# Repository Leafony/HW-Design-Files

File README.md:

# License

These files are licensed under a [Creative Commons Attribution license(CC-BY)](https://creativecommons.org/licenses/by/4.0/).

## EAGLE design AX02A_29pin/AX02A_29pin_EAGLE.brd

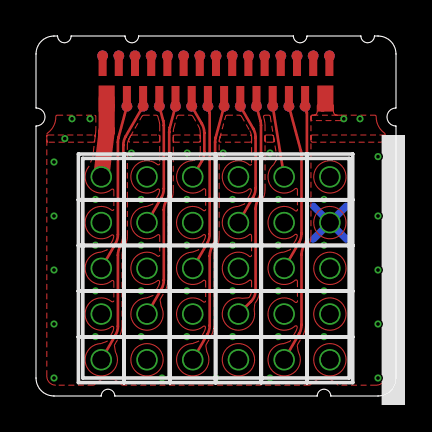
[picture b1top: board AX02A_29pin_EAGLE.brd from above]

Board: 4 copper layers, 20.0 x 20.0 mm, 31 parts (0 on the bottom side), 29 nets.

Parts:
CN561: PW10180TD
DP561, DP562, DP563, DP564, DP565, DP566, DP567, DP568, DP569, DP570, DP571, DP572, DP573, DP574, DP575, DP576, DP577, DP578, DP579, DP580, DP581, DP582, DP583, DP584, DP585, DP586, DP587, DP588, DP589, DP590: DP002T

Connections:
A0: CN561.B6, CN561.F6, DP566.1
A1: CN561.B8, CN561.F8, DP568.1
A2: CN561.B10, CN561.F10, DP570.1
A3: CN561.B12, CN561.F12, DP572.1
A4: CN561.B14, CN561.F14, DP574.1
A5: CN561.B16, CN561.F16, DP576.1
AREF: CN561.B4, CN561.F4, DP564.1
D0: CN561.B18, CN561.F18, DP578.1
D1: CN561.B20, CN561.F20, DP580.1
D2: CN561.B22, CN561.F22, DP582.1
D3: CN561.B24, CN561.F24, DP584.1
D4: CN561.B26, CN561.F26, DP586.1
D5: CN561.B28, CN561.F28, DP588.1
D6: CN561.B7, CN561.F7, DP567.1
D7: CN561.B9, CN561.F9, DP569.1
D8: CN561.B11, CN561.F11, DP571.1
D9: CN561.B13, CN561.F13, DP573.1
D10: CN561.B15, CN561.F15, DP575.1
D11: CN561.B17, CN561.F17, DP577.1
D12: CN561.B19, CN561.F19, DP579.1
D13: CN561.B21, CN561.F21, DP581.1
GND: CN561.B27, CN561.F27, DP587.1
P3R3V: CN561.B1, CN561.F1, DP561.1
RESET: CN561.B5, CN561.F5, DP565.1
SCL: CN561.B25, CN561.F25, DP585.1
SDA: CN561.B23, CN561.F23, DP583.1
SWCLK: CN561.B29, CN561.F29, DP589.1
SWDIO: CN561.B2, CN561.F2, DP562.1
VBUS: CN561.B3, CN561.F3, DP563.1

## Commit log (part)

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2022-02-03 Add files via upload
    Add resistor(R127)
2024-07-25 add AC07 LoRa Mary
2024-07-25 add AC07 layout & sch pdf
2024-07-25 ドキュメントを追加
2025-02-26 チップアンテナ化に伴う変更
2025-02-26 実装図新規作成
2025-02-26 LTE-M_Maryディレクトリ作成
2025-04-30 スイッチの向き追加
